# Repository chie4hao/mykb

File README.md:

# mykb
My very first keyboard PCB!

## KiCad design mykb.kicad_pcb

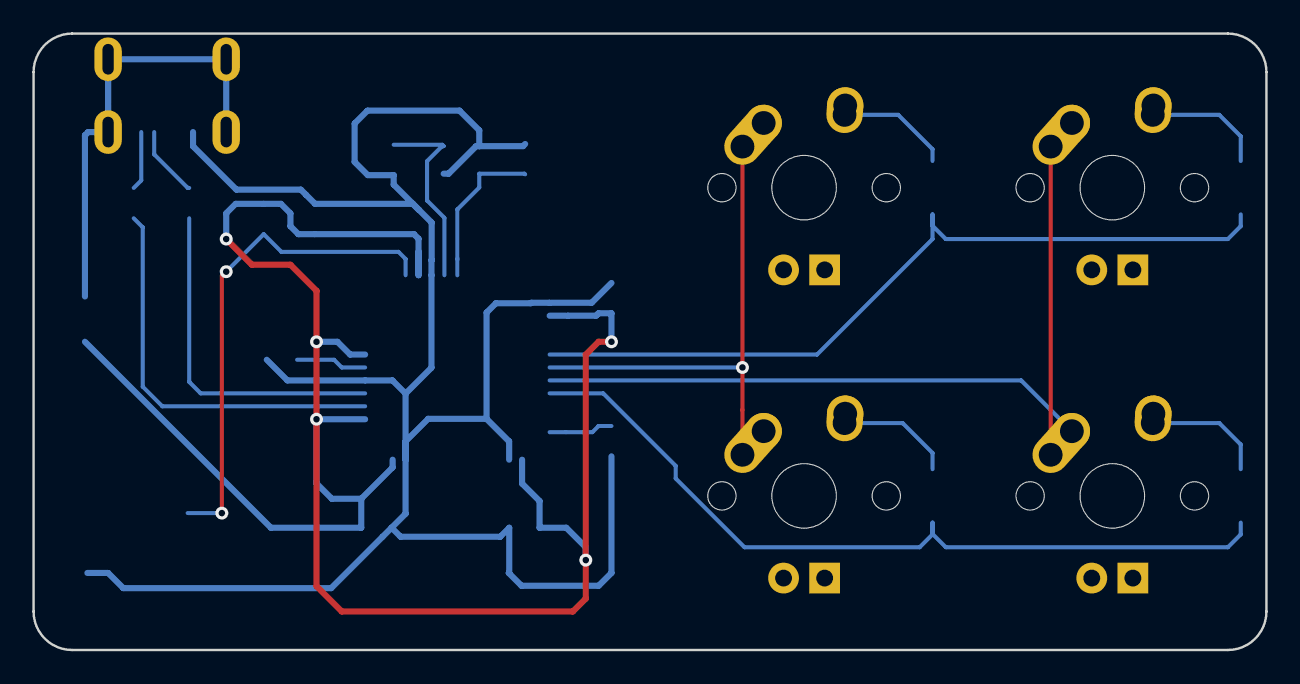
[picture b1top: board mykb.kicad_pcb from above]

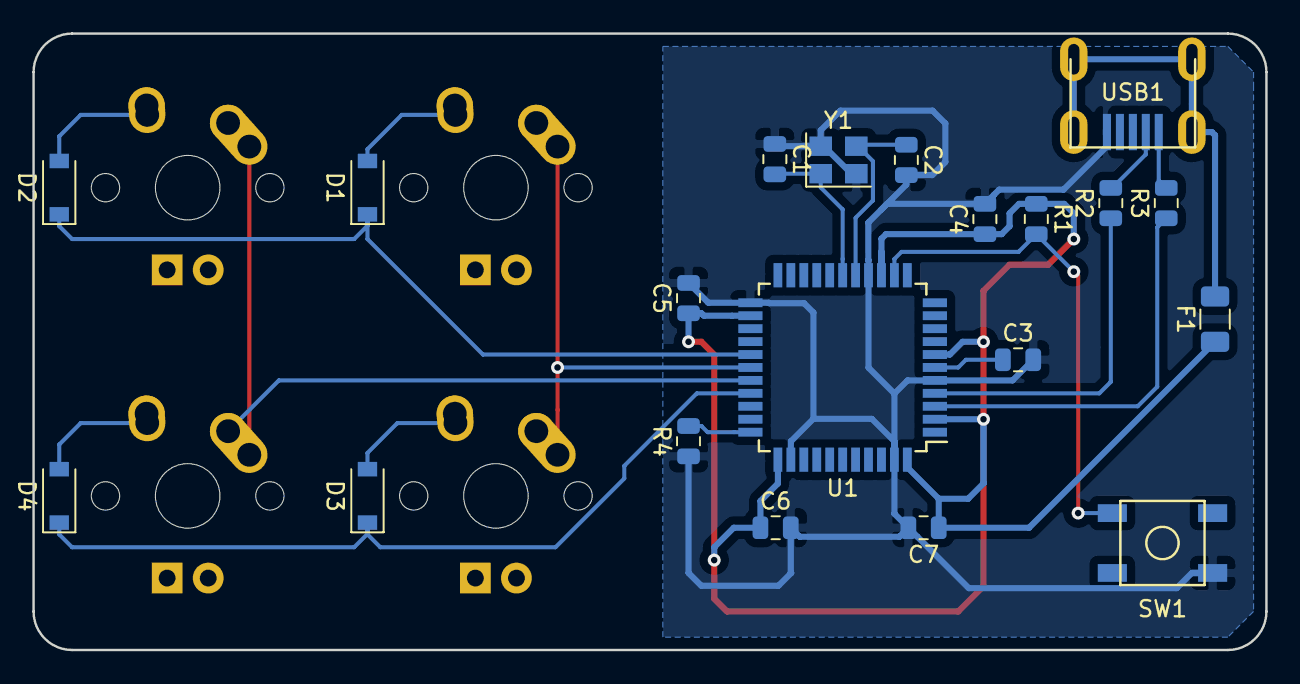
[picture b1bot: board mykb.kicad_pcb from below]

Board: 2 copper layers, 76.2 x 38.1 mm, 24 parts (20 on the bottom side), 20 nets.

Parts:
C1, C2: 22pF; C_0805_2012Metric
C3: 1uF; C_0805_2012Metric
C4, C5, C6: 0.1uF; C_0805_2012Metric
C7: 10uF; C_0805_2012Metric
D1, D2, D3, D4: SOD-123; D_SOD-123
F1: 500mA; Fuse_1206_3216Metric
MX1, MX2, MX3, MX4: MX-1U
R1, R4: 10k; R_0805_2012Metric
R2, R3: 22; R_0805_2012Metric
SW1: SW_Push; SKQG-1155865
U1: ATmega32U4-AU; TQFP-44_10x10mm_P0.8mm
USB1: Molex-0548190589
Y1: 16MHz; Crystal_SMD_3225-4Pin_3.2x2.5mm

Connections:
+5V: C4.1, C5.1, C6.1, C7.1, F1.1, R1.1, U1.2, U1.7, U1.14, U1.24, U1.34, U1.44
COL0: MX1.1, MX3.1, U1.28
COL1: MX2.1, MX4.1, U1.29
D+: R2.2, USB1.4
D-: R3.2, USB1.5
GND: C1.1, C2.2, C3.2, C4.2, C5.2, C6.2, C7.2, R4.1, SW1.1, U1.5, U1.15, U1.23, U1.35, U1.43, USB1.1, Y1.2, Y1.4
unnamed: C1.2, U1.17, Y1.1
unnamed: C2.1, U1.16, Y1.3
unnamed: C3.1, U1.6
unnamed: D1.2, MX1.2
unnamed: D2.2, MX2.2
unnamed: D3.2, MX3.2
unnamed: D4.2, MX4.2
unnamed: R1.2, SW1.2, U1.13
unnamed: R2.1, U1.4
unnamed: R3.1, U1.3
unnamed: R4.2, U1.33
ROW0: D1.1, D2.1, U1.27
ROW1: D3.1, D4.1, U1.30
VCC: F1.2, USB1.6

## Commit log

2019-03-24 add new files
2019-03-24 change project directory
2019-03-24 Add submodules
2019-03-24 new file: fp-lib-table sym-lib-table
2019-03-24 Celebration!
2019-03-24 add a.dxf
